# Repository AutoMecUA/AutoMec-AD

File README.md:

# AutoMec AD

<<<<<<< HEAD
This repository serves as the main repository for the autonomous RC car team of AutoMec. The repository consist of ML code
for the lane detection, template matching code for signal recognition, all incorporated in a ROS framework.
=======
>>>>>>> 40254a4244cb09b758f7b297e9e651befd35b496

This repository serves as the main repository for the autonomous RC car team of AutoMec AD. 
The software developed uses a CNN for lane detection and template matching for signal recognition.
All the software is incorporated into the ROS framework.
<br>
<br>

## How to run:

All the setup, commands and methods used are described in the [wiki](https://github.com/AutomecUA/AutoMec-AD/wiki). <br>

This is still a WIP. Some errors are to be expected. If you have any doubts or want to report a bug,
feel free to use the Issues or [send us an email](mailto:dem-automec@ua.pt)!

<<<<<<< HEAD
## Quick cheat-sheet

To correctly run this code, please insert in your .bashrc/.zshrc:

```
export GAZEBO_MODEL_PATH="`rospack find prometheus_gazebo`/models:${GAZEBO_MODEL_PATH}"
export automec_developer="*place your name here"
```

And please install the following dependencies:

```
sudo apt-get install ros-noetic-ros-controllers ros-noetic-ackermann-msgs ros-noetic-navigation
```

And place the following package inside your workspace:

https://github.com/CIR-KIT/steer_drive_ros (on the `melodic-devel`)

To run the gazebo arena:
```
roslaunch prometheus_gazebo arena.launch
```

To run the signal panel:

```
roslaunch prometheus_gazebo signal_panel.launch
```

To launch the car in simulation:
```
roslaunch prometheus_bringup bringup.launch sim:=true
```

Optionally, you can also add some visualization, and control with a game console controller:

```
roslaunch prometheus_bringup bringup.launch sim:=true visualize:=true controller:=true
```

You can also change the linear velocity:

```
roslaunch prometheus_bringup bringup.launch sim:=true linear_velocity:=0.5
```

To write the dataset:

```
roslaunch prometheus_driving dataset_writing.launch
```

To train the model, run the script `ml_training.ipynb`, from package `prometheus_driving` in a jupyter notebook. 

To run the dataset:

```
roslaunch prometheus_driving ml_driving.launch model:=*insert model name*
```

And to launch the signal detection:

```
roslaunch prometheus_signal_recognition signal_recognition.launch 
```

If you want to run the model without using the signal detection, please launch the following command to start the driving:

```
rostopic pub /signal_detected std_msgs/String "pForward"
```

If you want to run the complete driving experience, please use:

```
roslaunch prometheus_bringup main_driving.launch model_name:=*insert model name*
```
=======

## Simulation Environment:
The software is developed and tested on a virtual environment named Gazebo. 

## Challenges
The autonomous vehicle aims to:
- Drive autonomously in a closed circuit
- Avoid objects
- Detect traffic lights and vertical signals
- Autonomously park

### Driving

### Parking 

>>>>>>> 40254a4244cb09b758f7b297e9e651befd35b496

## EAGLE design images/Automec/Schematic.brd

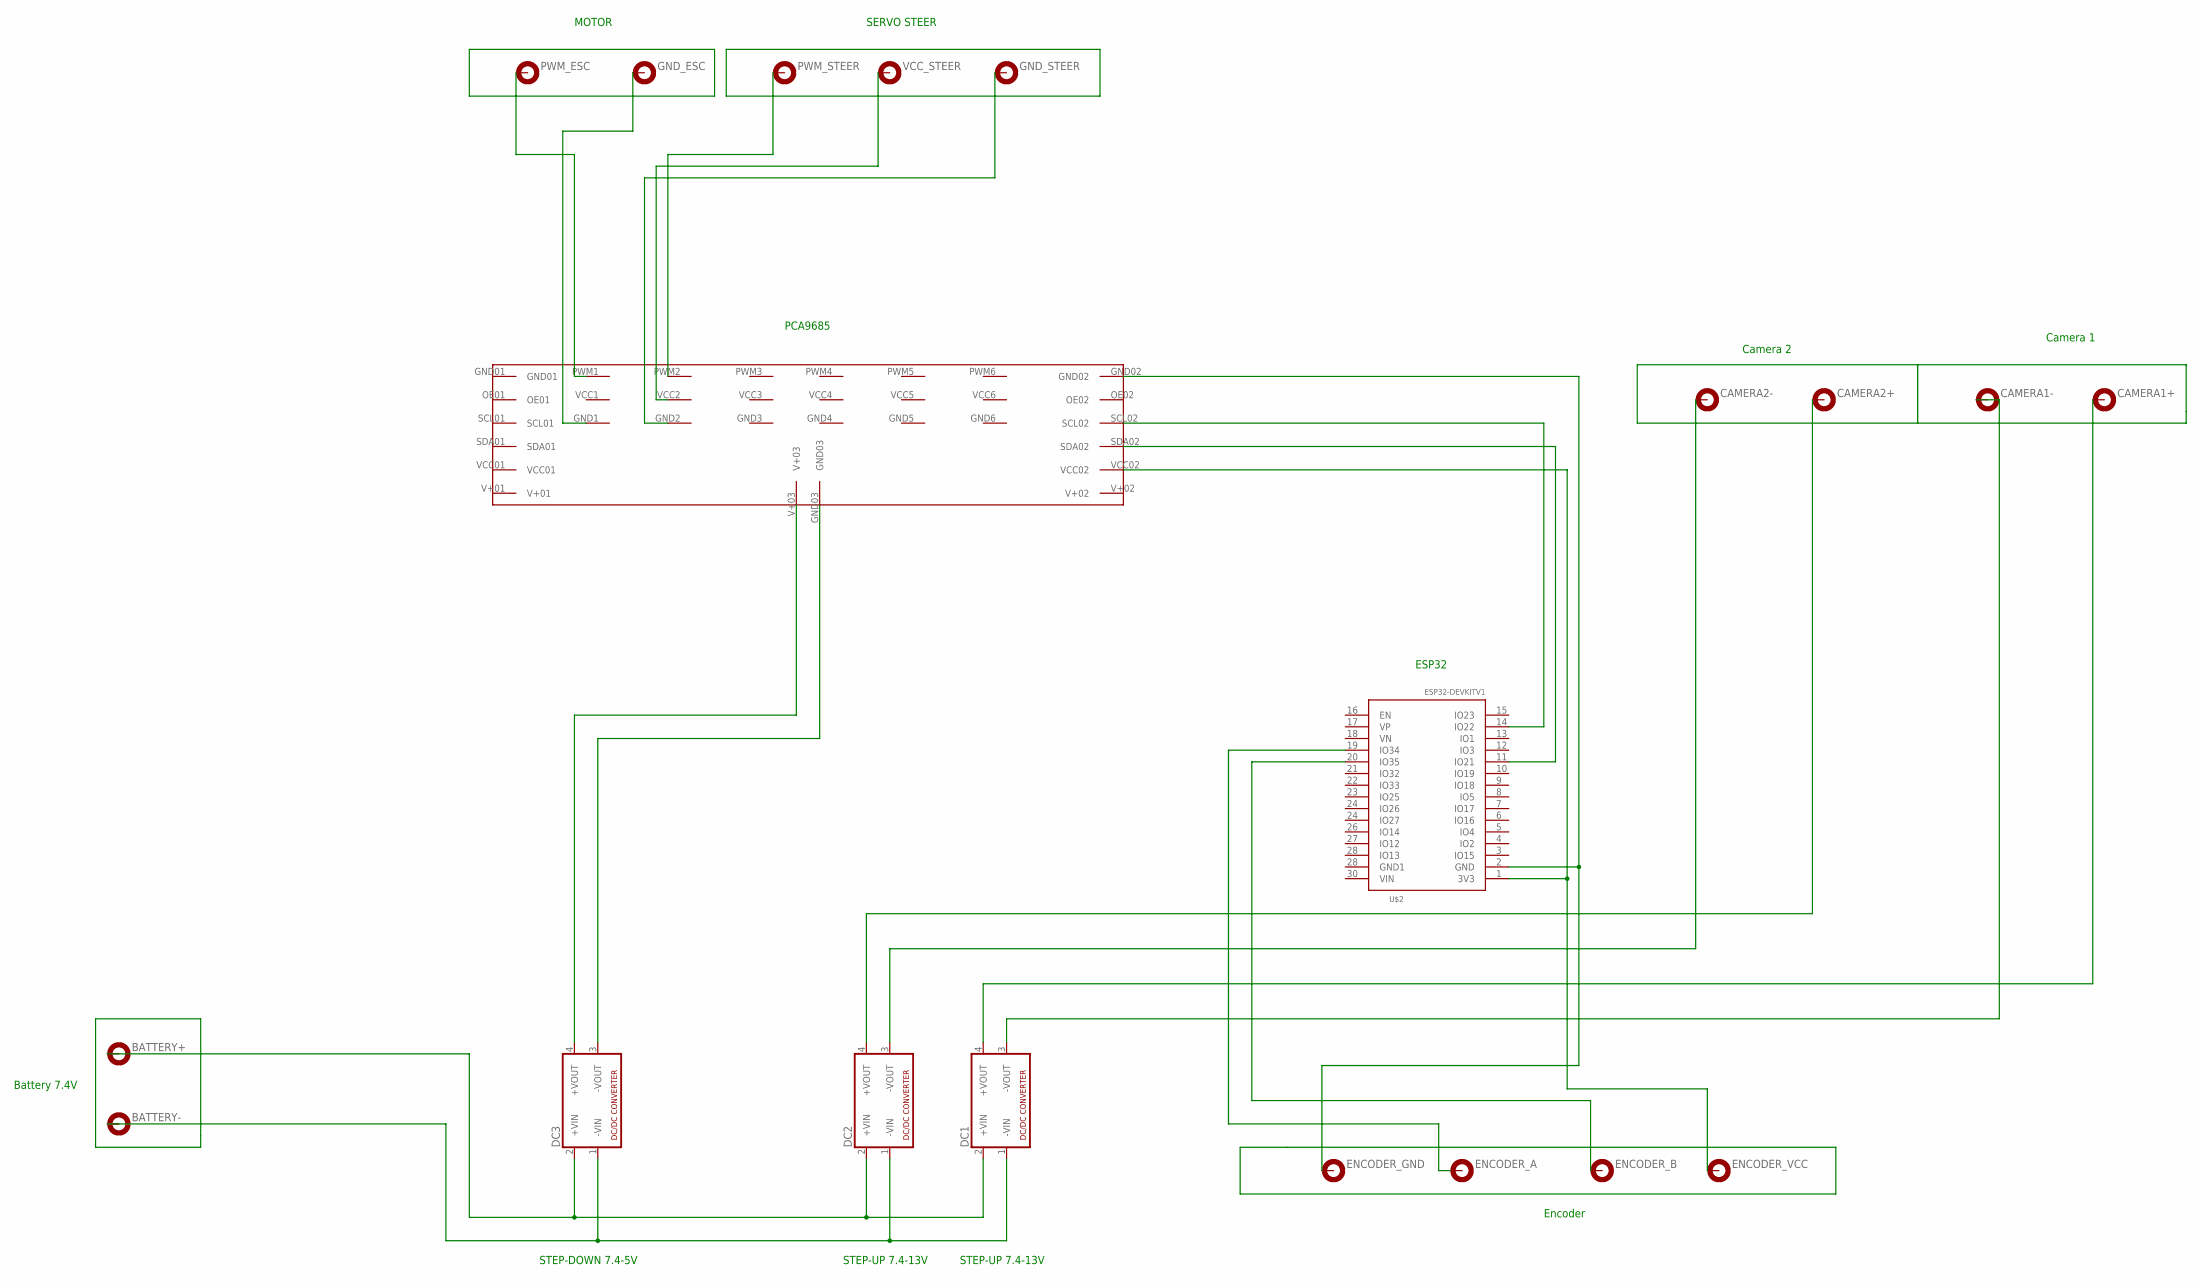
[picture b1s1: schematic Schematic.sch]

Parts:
BATTERY+: MOUNT-PAD-ROUND2.8; 2,8-PAD
BATTERY-: MOUNT-PAD-ROUND2.8; 2,8-PAD
CAMERA1+, CAMERA1-, CAMERA2+, CAMERA2-: MOUNT-PAD-ROUND2.8; 2,8-PAD
DC1, DC2, DC3: NME
ENCODER_A: MOUNT-PAD-ROUND2.8; 2,8-PAD
ENCODER_B: MOUNT-PAD-ROUND2.8; 2,8-PAD
ENCODER_GND: MOUNT-PAD-ROUND2.8; 2,8-PAD
ENCODER_VCC: MOUNT-PAD-ROUND2.8; 2,8-PAD
GND_ESC: MOUNT-PAD-ROUND2.8; 2,8-PAD
GND_STEER: MOUNT-PAD-ROUND2.8; 2,8-PAD
PWM_ESC: MOUNT-PAD-ROUND2.8; 2,8-PAD
PWM_STEER: MOUNT-PAD-ROUND2.8; 2,8-PAD
U$1: PCA9685PCA9685; DIP5918W53P254L2279H300Q12B
U$2: ESP32DEVKITV1; ESP32-DEVKITV1
VCC_STEER: MOUNT-PAD-ROUND2.8; 2,8-PAD

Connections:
unnamed: ENCODER_GND.B2,8, U$1.GND02, U$2.2 (GND)
unnamed: ENCODER_VCC.B2,8, U$1.VCC02, U$2.1 (3V3)
unnamed: U$1.SCL02, U$2.14 (IO22)
unnamed: U$1.SDA02, U$2.11 (IO21)
unnamed: BATTERY-.B2,8, DC1.1 (-VIN), DC2.1 (-VIN), DC3.1 (-VIN)
unnamed: BATTERY+.B2,8, DC1.2 (+VIN), DC2.2 (+VIN), DC3.2 (+VIN)
unnamed: CAMERA1-.B2,8, DC1.3 (-VOUT)
unnamed: CAMERA1+.B2,8, DC1.4 (+VOUT)
unnamed: CAMERA2+.B2,8, DC2.4 (+VOUT)
unnamed: CAMERA2-.B2,8, DC2.3 (-VOUT)
unnamed: DC3.3 (-VOUT), U$1.GND03
unnamed: DC3.4 (+VOUT), U$1.V+03
unnamed: ENCODER_A.B2,8, U$2.19 (IO34)
unnamed: ENCODER_B.B2,8, U$2.20 (IO35)
unnamed: PWM_ESC.B2,8, U$1.PWM1 (PWM$1)
unnamed: GND_ESC.B2,8, U$1.GND1 (GND$1)
unnamed: PWM_STEER.B2,8, U$1.PWM2 (PWM$2)
unnamed: U$1.VCC2 (VCC$2), VCC_STEER.B2,8
unnamed: GND_STEER.B2,8, U$1.GND2 (GND$2)

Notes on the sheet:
ESP32
STEP-UP 7.4-13V
STEP-DOWN 7.4-5V
PCA9685
Camera 1
Camera 2
Encoder
Battery 7.4V
MOTOR
SERVO STEER

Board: 2 copper layers, 20 parts (0 on the bottom side), 19 nets, no tracks yet.

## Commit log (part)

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2021-08-12 deleted the obsolete robot 03
2021-08-13 launch fies & drive2av.py update + issue 28
2021-08-23 Changed requirements.txt
2021-08-25 Revert " change to the camera id"
    This reverts commit f0561fa649da26a73040199b3efb9df33ed36dc5.
2021-08-26 changed the camera id in the write launch
2021-08-26 added button image to wiki
2021-08-30 Change write.py and consequent launch files in order to record boolean velocity in real car.
2021-09-02 Added Stitchers
2021-09-04 Updated StitcherFunction for more versatility
2021-09-08 Cam config img
2021-09-09 fix cap.release() issue
2021-09-09 update StitcherSimulation.py (1st working version)
    have problems. it doesnt stitche at same place.
2021-09-16 Changed button from press to switch
2021-09-17 add jpg file to kinect mesh
2021-09-17 issue 46, gitignore jpg's
2021-09-17 add kinect jpg (due to issue 46)
2021-09-17 Changed .gitignore to allow images but disallow all files on cnn/data and cnn/models
2021-09-17 issue 41 (wip), kinect gazebo update
2021-09-18 issue 41, dual kinect gazebo
2021-09-23 issue 50 (check first aproach)
2021-09-25 add ipm working
2021-09-26 Rename odom2 to ipm2.py
2021-09-26 Add images for wiki (branch piggyback commit)
2021-09-27 Created a new publisher on AndroidConversor.py which converts the "press" button we have on ROS Mobile to a "switch" button. This does not interfere with all the other uses of this script. Launch fil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
2021-09-28 first ipm optimization
2021-09-28 fix another datetime error
2021-09-28 add ipm optimized
2021-09-28 Timing processes
2021-09-28 fix performace of ipm to 0.15s
2021-09-30 fix error dividing by 0 in train2a_transfer_learning.py
2021-09-30 issue 63, change wheel color to darkgray on gazebo
2021-10-01 added driving launch with cnn2 + kinectic
2021-10-02 New launch files for cnn_tf
2021-10-03 IPM class v1.0.0
2021-10-06 Compatibility enlarged to cnn1 on physical
2021-10-06 Bug fix to last commit
2021-10-06 Update branch with dev's images (#77)
    * Change write.py and consequent launch files in order to record boolean velocity in real car.
    * Change write.py and consequent launch files in order to record boolean velocity in real car.
    * Bug fix to run real car with velocity first
    * Show Robot View as file is recording
    * fix cap.release() issue
    * issue 40 (yaml files)
2021-10-07 urdf models update
2021-10-08 It is now compatible to cnn2a on simulation
2021-10-08 Removed unused launch file
2021-10-08 Compatible with cnn2 physical
2021-10-10 Imported images from new_ipm
2021-10-13 issue #73, correct gazebo camera to 640x480
2021-10-13 Issue #86, New lane_detection package
2021-10-13 Introduced a threshold to only publish on /signal_vel after a few consecutive signal detections
2021-10-14 issue 88, missing folder on lane_detection
2021-10-20 hotfixes for launch file without kinects
2021-10-22 Creates log file for signal recognition, with the signal detected and it's resolution
2021-10-27 Create new folder for log files and rounded the percentages
2021-10-27 added updated rqt_graph
2021-11-06 posicion_camera
2021-11-29 #105 Creation of IPM package, creation of launch file and an IMP ROS compatible script
2021-12-04 #105 Added lib directory and changed .gitignore
2021-12-04 #105 Although it does not implement IPM well, it doesn't crash, so that's a progress.
2021-12-04 #105 Corrections on class
2021-12-04 #105 Changed debug mode
2021-12-04 #105 Changed IPM class to receive a dictionary with the pose of the camera and calculating the extrinsic matrix based on it
2021-12-08 Added color masking to signal recognition
2021-12-14 #110 Added toggle variable to activate or not the mask mode
2021-12-14 #110 Not mask mode is available on simulation
2021-12-20 #105 Added corner selection
2021-12-29 #32 Fixed launch file error.
2021-12-29 #32 Fixed bug on cnn1
2021-12-29 #32 Corrected signal recognition bug
2022-01-04 #110 Changing kinect to see image color
2022-01-08 Updated requirements.txt
2022-01-10 #120 first development in this issue, now code writs urdf to yaml files after writing
2022-01-19 Added support for joystick
2022-03-10 added software guide image
2022-03-18 #120 The code now gives the possibility to choose if you want to keep going even when the urdfs do not mach
2022-03-18 #120 The code is capable of distinguish simulation and real life models and compare them to the environment they are being used @manuelgitgomes
2022-04-22 Jupyter Notebook for ML modelling and testing
2022-04-24 #134 First tests with 2 webcams
2022-04-24 Added sleep
2022-04-27 #134 small bug fix
2022-04-29 mask changes
2022-04-29 HOTFIX for lack of red detections
2022-04-30 Driving1 logic for parking added
2022-04-30 Added parking to signals
2022-04-30 TIme out developments
2022-04-30 driving py change
2022-04-30 Added signal logs to git ignore
2022-05-15 Adds new packages and removes unwanted launch files #143
2022-05-22 #143 changed cam_angle and cam_height to cam_pose
2022-05-22 #143 Remove stitcher
2022-05-22 #143 yaml added
2022-05-23 #143 Linting and reduced repetition w/ list comprehension
2022-05-29 automatic dataset naming generation
2022-05-30 implemented 'q' to quit gazebo and save dataset
2022-06-05 #143 improvements: q[uit] and s[ave] with **confirmation**, richer yaml date entry
2022-06-07 #143 Replaced all global vars into function arguments
    PS: We have to make sure that the argument vars in message_RGB_ReceivedCallback are changed in the callee function (main) as well
2022-07-18 #143 Fixed parameters and added sensors
2022-07-25 refactor(driving1 and write): #143 Switched globals to dict
    Also refactor to sourcery.ai's suggestions
2022-08-01 #143 changed urdf
2022-08-01 #143 Add kinect.launch
2022-08-01 #143 corrections on simulation bringup
2022-08-08 #143 added compatibility between real and simulated environment
2022-08-08 chore(crosswalk lib): Updated mp4 files to gitignore
2022-08-08 #143 dataset writing on simulation
2022-08-10 #143 Removing some old packages, adding joystick support, optimizing training script and augmenting compatibility between real and simulation
2022-08-13 feat(crosswalk lib): #154 Added fps to frame description stdout line
    Other minor tweak: waitkey delay was changed from infinite to 1ms
2022-08-13 refactor(crosswalk package): #154 Added crosswalk stateful abstract function
    Also, separated all source code into stateless or stateful related
2022-08-13 refactor(crosswalk package): #154 Added new stateful algorithm's base structure
    Approach for this one will be using particle filters concepts
2022-08-22 #143 Adding new signal recognition
2022-09-05 #143 Sequential detection bettered on signal recognition, driving reformulated.
2022-09-12 #143 Updated Readme
2022-09-12 HOTFIX remove legacy code
2022-09-19 Dev (#161)
    * Adds new packages and removes unwanted launch files #143
    * #143 Package prometheus_gazebo done
    * #143 Remove stitcher
    * #143 prometheus_gazebo hotfix
    * #143 Linting and reduced repetition w/ list comprehension
    * #143 Added robot simulation
2022-09-19 #154 Plugged in crosswalk detection within robot's script
    Also: Deleted unused functions
2022-10-10 Signal display fix #160
2022-10-26 HOTFIX changed win type from autosize to normal in dataset writing
2022-11-11 Changed mask mode from RGB to HSV
2022-11-16 Fixed ipynb script
2022-11-20 Added R2 trigger to accelerate on gazebo simulation and limited turning angle in twist cap script to prevent drifting
2022-11-23 Panel centered and tilted 25 degrees #154
2022-11-26 #156 added velociy Repeater
2022-11-29 Remove directory
2022-11-30 added the ros interface with arduino
2022-12-05 upgrade crosswalk detection #154
2022-12-07 #172 Started foot recognition
2022-12-09 #172 Cleaned code to work with classes, as its more concise and easier to read
2022-12-12 publish topic of encoder
2022-12-12 #172 Coisas
2022-12-14 code cleanup: crosswalk
2023-01-01 feat: add complex cnns
2023-01-02 Imp/requirements (#177)
    * #155 Update requirements with minor printing errors
    * Closes #155 - ends undesirable prints.
2023-01-15 readme: Add images for marketing value
2023-01-15 Changes in readme
2023-01-16 Read me update (#182)
    * readme: Add images for marketing value
    * readme: compressed gifs
    * Changes in readme
    * Added new gazebo image
2023-02-01 fixed signals.world
2023-02-07 changed dataset path
2023-02-08 trying suggested models with pytorch
2023-02-08 added new model
2023-02-08 changed driving with model to pytorch
2023-02-08 try points 2D to 3D
2023-02-09 code reorganization
2023-02-09 added yaml file generation when saving model #165
2023-02-09 changed yaml file name
2023-02-12 added environment variable #165
2023-02-12 added enviromnt variable to dataset writing
2023-02-12 fixed save model
2023-02-12 added learning rate step #165
2023-02-12 changed default weight decay
2023-02-12 fixed vgg model
2023-02-13 Checking the project points function
2023-02-14 modifying plots to represent better the errors
2023-02-14 removed title
2023-02-15 #176 Correction of point transformation error
2023-02-15 removed argument
2023-02-18 implemented automatic labeling
2023-02-20 implemented automatic labeling #176
2023-02-21 created a simple lstm #165
2023-02-21 changed visualization to degrees
2023-02-22 I think previous lstm network was wrong
2023-02-24 added option to sumarize model to easily visualize it
2023-02-24 added option to draw the model when -sm is used
2023-02-27 added model.train and model.eval to prevent dropout in the testing
2023-02-27 changed model.eval() and model.train() according to documentation
2023-02-28 added batchnorm to nvidia and rota #165
2023-03-01 generalizing controller setup
2023-03-02 added subscriber to change model used #165
2023-03-09 added resnet import to main driving script
2023-03-10 signal word - only cattle signal
2023-03-11 signal world - only Other_Dangers_signal
2023-03-16 created a package for semantic segmentation
2023-03-16 displays the image with different color based on the label id
2023-03-28 test using yolop
2023-03-29 changed how the model saving criteria to check the test loss instead of the training loss and plot a line where the last save happened
2023-04-05 yolov5s training code #176
2023-04-09 added mask to visualization training script
2023-04-09 fixed the saving names
2023-04-12 Depth functions were added #172
2023-04-15 created a network based on segnet but with the inputs from encoder part
2023-04-15 finished creating scripts for semantic segmentation
2023-04-16 added brightness augmentation
2023-04-17 #188 bug fix in model names
2023-04-17 Restoring gitignore
2023-04-19 clean detection code #176
2023-05-10 aded a working transfirmer
2023-05-11 added topic for changing model when launching segmentation
2023-05-18 updated servos limit information
2023-05-20 Implemented neural network scripts to train and deploy models for driving the car and for semantic segmentation (#193)
    * feat: add complex cnns
    * changed dataset path
    * trying suggested models with pytorch
    * implemented visualization and fixed model
    * added new model
    * fixed images color when displaying
2023-05-25 fixes forem real test
2023-05-26 addapted driving to use the previous implemtnations
2023-06-05 added schematic png to render in wiki
2023-06-05 updated png schematic
2023-06-05 updated semantic segmentation code to be similar as the driving
2023-06-05 removed unused imports
2023-06-28 specified which camera to use by the serial id in hte bringup file
2023-06-28 fixed value to go backwards
2023-07-09 commented the decision maker script
2023-08-02 Added option to set variable velocity in the bringup
2023-08-02 Added variable backward movement and L2 trigger to move back
2023-08-05 #192 Its working but should not be merged because its a still,development version, would break if the user would try to train or use other models with a single image input
2023-08-07 then it is to delete this script
2024-01-28 Added vertical traffic sign recognition code using YOLOv5 #176
